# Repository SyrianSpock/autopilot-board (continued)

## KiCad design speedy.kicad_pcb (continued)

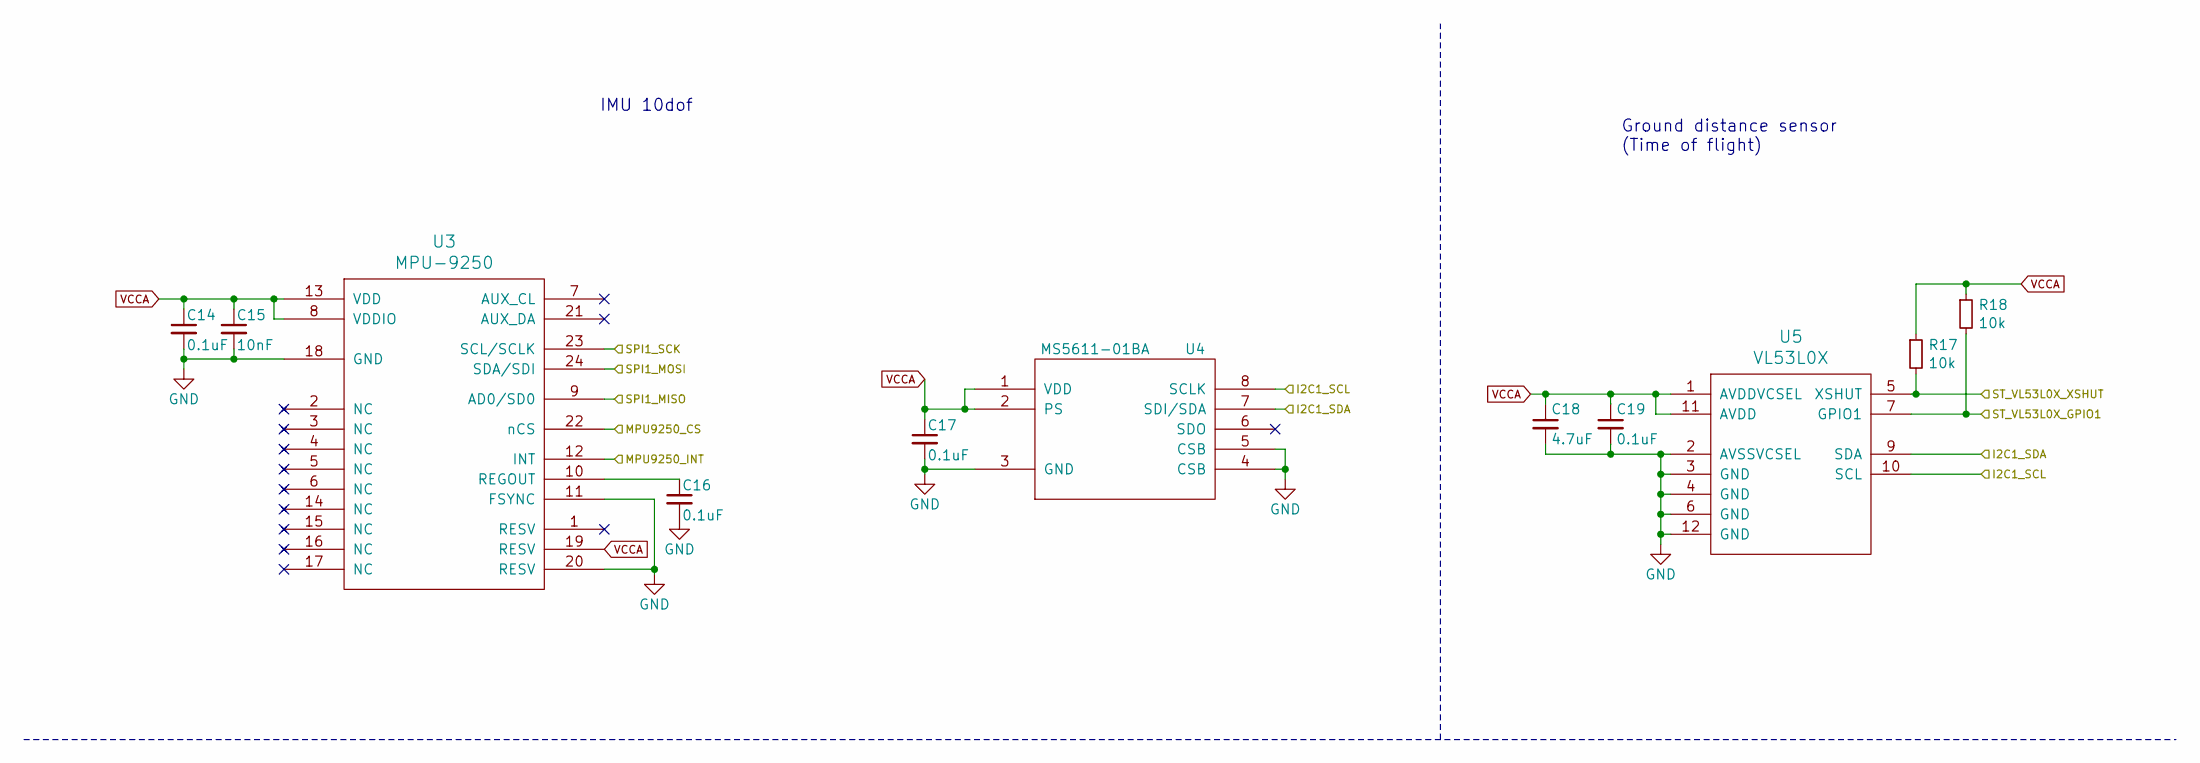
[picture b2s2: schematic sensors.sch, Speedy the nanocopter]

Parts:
C14, C16, C17, C19: 0.1uF; _0402
C15: 10nF; _0402
C18: 4.7uF; _0402
R17, R18: 10k; _0402
U3: MPU-9250; _MPU-9XX0
U4: MS5611-01BA; _MS5611-01BA
U5: VL53L0X; ST-VL53L0X

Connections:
/I2C1_SCL: U4.8 (SCLK), U5.10 (SCL); also elsewhere on the board
/I2C1_SDA: U4.7 (SDI/SDA), U5.9 (SDA); also elsewhere on the board
/MPU9250_CS: U3.22 (nCS); also elsewhere on the board
/MPU9250_INT: U3.12 (INT); also elsewhere on the board
/SPI1_MISO: U3.9 (AD0/SD0); also elsewhere on the board
/SPI1_MOSI: U3.24 (SDA/SDI); also elsewhere on the board
/SPI1_SCK: U3.23 (SCL/SCLK); also elsewhere on the board
/TOF_GPIO1: R18.2, U5.7 (GPIO1); also elsewhere on the board
/TOF_XSHUT: R17.2, U5.5 (XSHUT); also elsewhere on the board
GND: C14.2, C15.2, C16.2, C17.2, C18.2, C19.2, U3.11 (FSYNC), U3.18 (GND), U3.20 (RESV), U4.3 (GND), U4.4 (CSB), U4.5 (CSB), U5.2 (AVSSVCSEL), U5.3 (GND), U5.4 (GND), U5.6 (GND), U5.12 (GND); also elsewhere on the board
unnamed: C16.1, U3.10 (REGOUT)
VCCA: C14.1, C15.1, C17.1, C18.1, C19.1, R17.1, R18.1, U3.8 (VDDIO), U3.13 (VDD), U3.19 (RESV), U4.1 (VDD), U4.2 (PS), U5.1 (AVDDVCSEL), U5.11 (AVDD); also elsewhere on the board

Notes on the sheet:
Ground distance sensor (Time of flight)
IMU 10dof

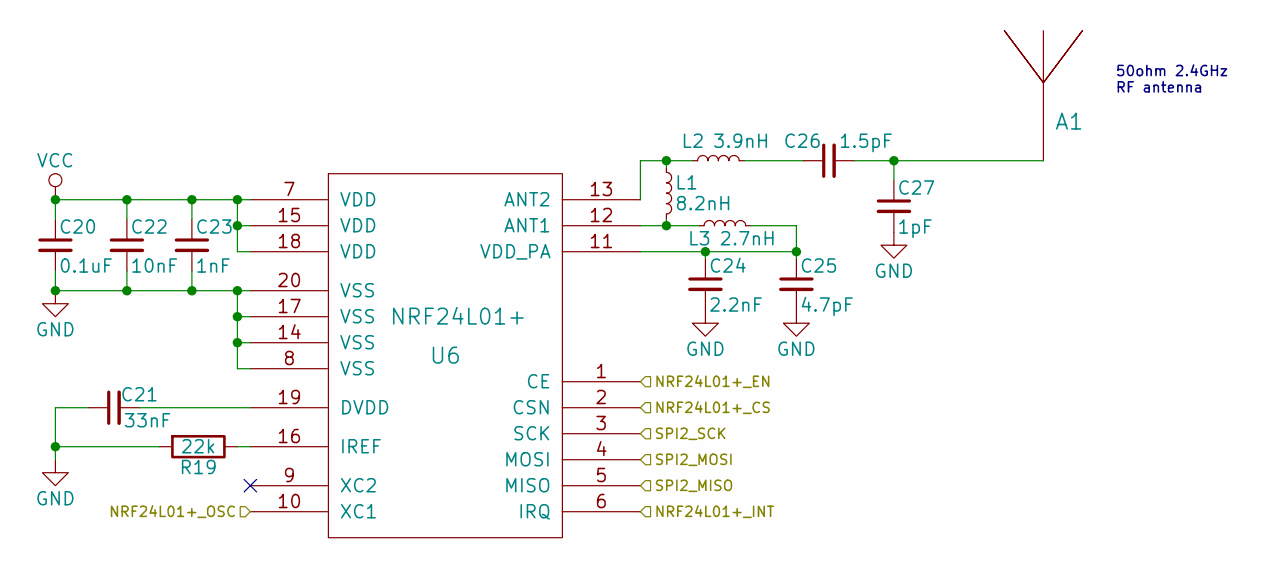
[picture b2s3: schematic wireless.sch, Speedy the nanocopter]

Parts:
A1: ANTENNA; _ANT-2.45-CHP
C20: 0.1uF; _0402
C21: 33nF; _0402
C22: 10nF; _0402
C23: 1nF; _0402
C24: 2.2nF; _0402
C25: 4.7pF; _0402
C26: 1.5pF; _0402
C27: 1pF; _0402
L1: 8.2nH; _0402
L2: 3.9nH; _0402
L3: 2.7nH; _0402
R19: 22k; _0402
U6: NRF24L01+; QFN-20-1EP_4x4mm_Pitch0.5mm

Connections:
/MCU_OSC_OUT: U6.10 (XC1); also elsewhere on the board
/NRF24L01+_CS: U6.2 (CSN); also elsewhere on the board
/NRF24L01+_EN: U6.1 (CE); also elsewhere on the board
/NRF24L01+_INT: U6.6 (IRQ); also elsewhere on the board
/SPI2_MISO: U6.5 (MISO); also elsewhere on the board
/SPI2_MOSI: U6.4 (MOSI); also elsewhere on the board
/SPI2_SCK: U6.3 (SCK); also elsewhere on the board
GND: C20.2, C21.1, C22.2, C23.2, C24.2, C25.2, C27.2, R19.2, U6.8 (VSS), U6.14 (VSS), U6.17 (VSS), U6.20 (VSS); also elsewhere on the board
unnamed: A1.1, C26.2, C27.1
unnamed: C21.2, U6.19 (DVDD)
unnamed: C24.1, C25.1, L3.2, U6.11 (VDD_PA)
unnamed: C26.1, L2.2
unnamed: L1.1, L2.1, U6.13 (ANT2)
unnamed: L1.2, L3.1, U6.12 (ANT1)
unnamed: R19.1, U6.16 (IREF)
VCC: C20.1, C22.1, C23.1, U6.7 (VDD), U6.15 (VDD), U6.18 (VDD); also elsewhere on the board

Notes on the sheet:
50ohm 2.4GHz RF antenna

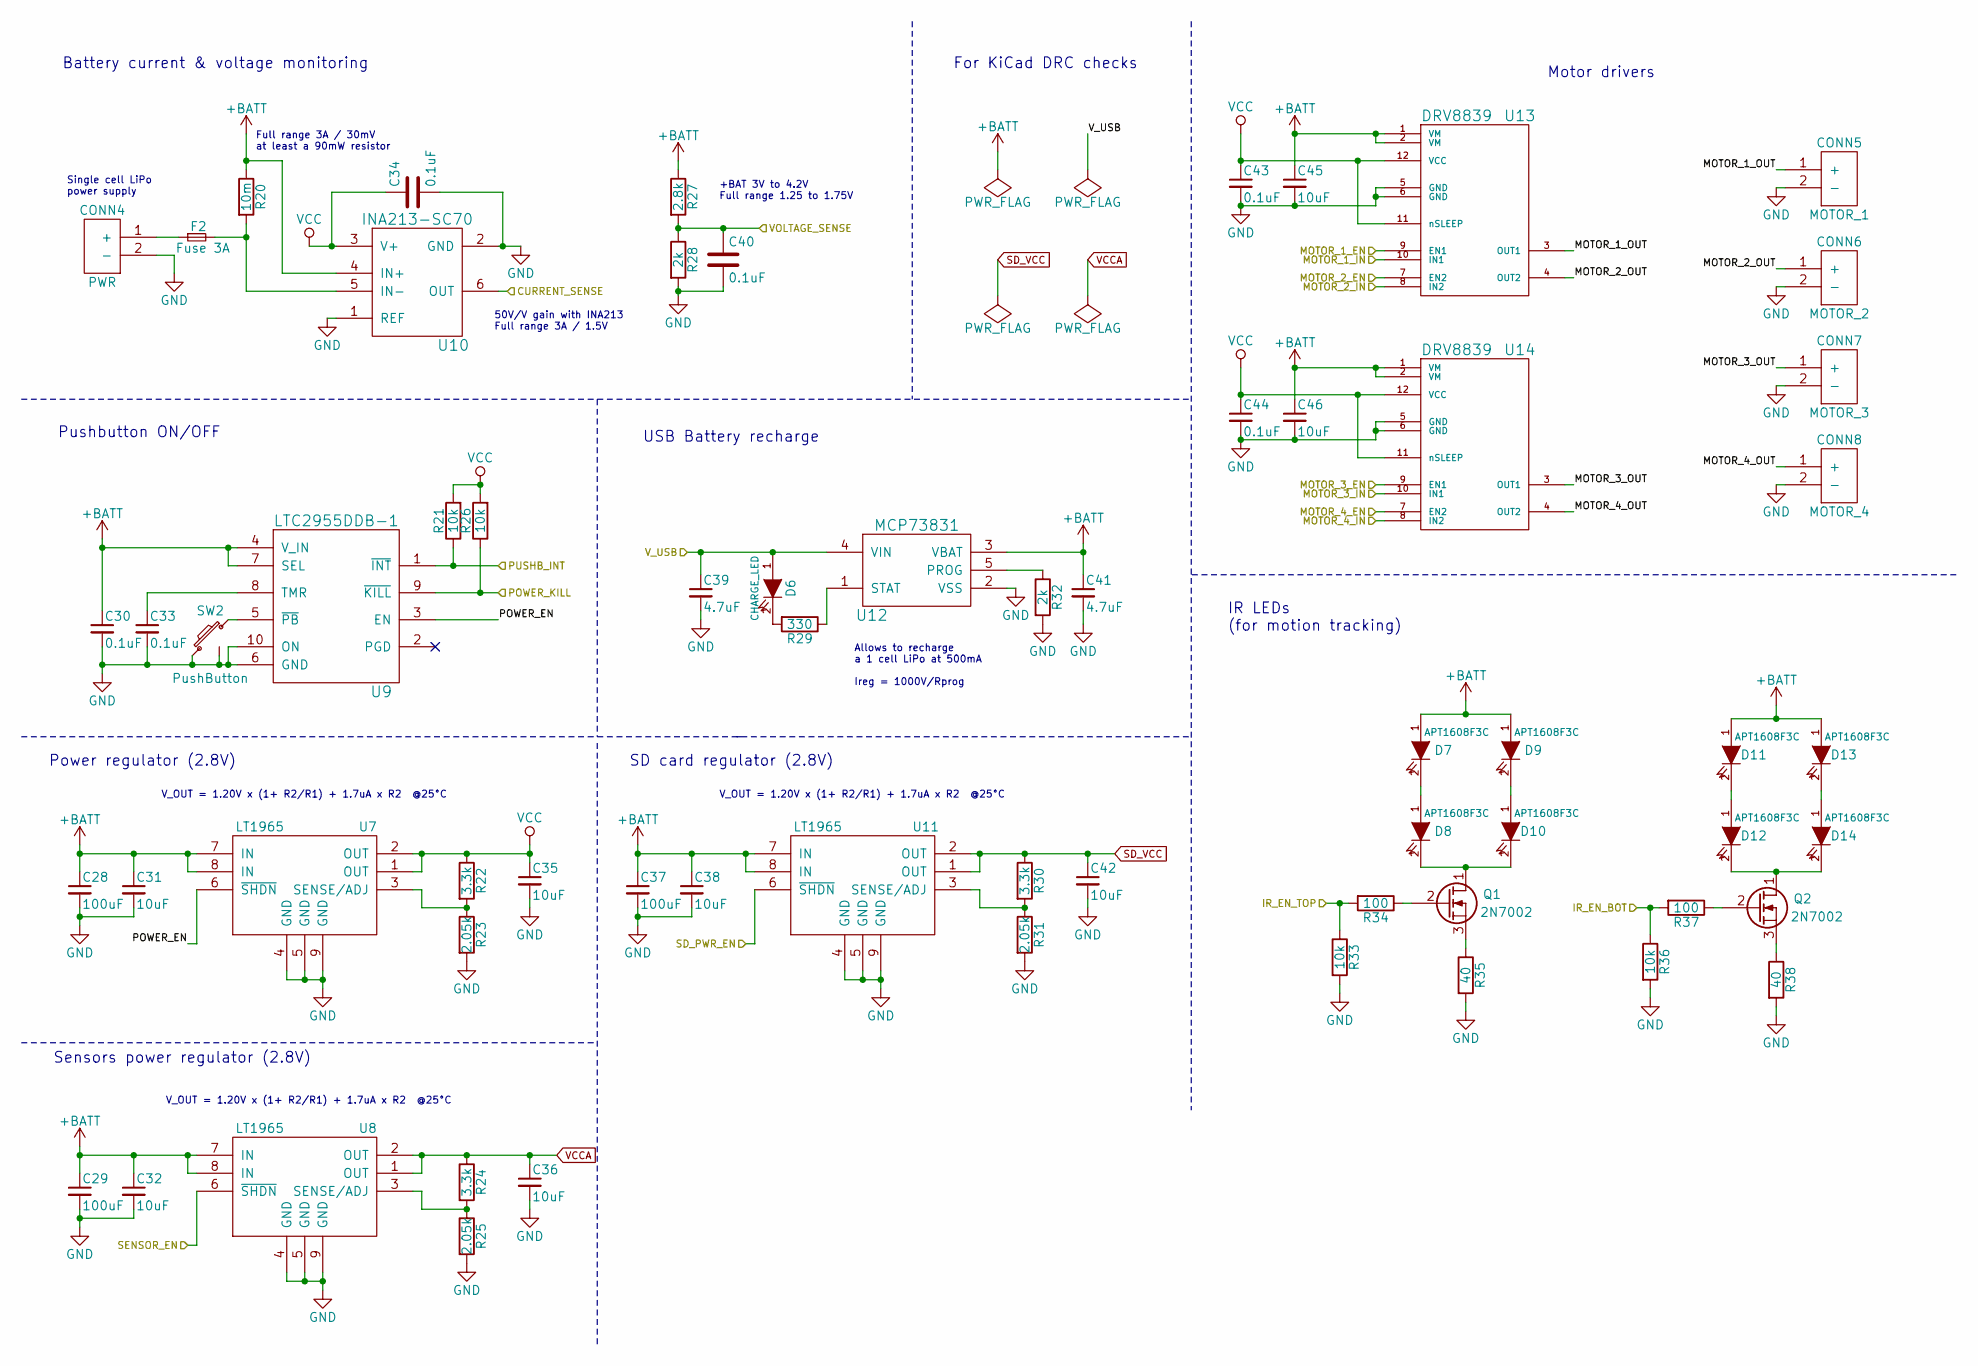
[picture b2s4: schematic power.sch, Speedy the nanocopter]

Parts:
C28, C29, C37: 100uF; _0603
C30, C33, C34, C40, C43, C44: 0.1uF; _0402
C31, C32, C35, C36, C38, C42, C45, C46: 10uF; _0603
C39, C41: 4.7uF; _0402
CONN4: PWR; _Pin2mm_2
CONN5: MOTOR_1; _Solder_Pad1.27_2
CONN6: MOTOR_2; _Solder_Pad1.27_2
CONN7: MOTOR_3; _Solder_Pad1.27_2
CONN8: MOTOR_4; _Solder_Pad1.27_2
D6: CHARGE_LED; _LED_0603
D7, D8, D9, D10, D11, D12, D13, D14: APT1608F3C; _LED_0603
F2: Fuse 3A; _0402
Q1, Q2: 2N7002; _SOT23-3
R20: 10m; _0402
R21, R26, R33, R36: 10k; _0402
R22, R24, R30: 3.3k; _0402
R23, R25, R31: 2.05k; _0402
R27: 2.8k; _0402
R28, R32: 2k; _0402
R29: 330; _0402
R34, R37: 100; _0402
R35, R38: 40; _0402
SW2: PushButton; SMD_Pushbutton_B3U-3100P
U7, U8, U11: LT1965; DFN-8-1EP_3x3mm_Pitch0.5mm
U9: LTC2955DDB-1; DFN-10-1EP_2x3mm_Pitch0.5mm
U10: INA213-SC70; SC70
U12: MCP73831; _TSOT23-5
U13, U14: DRV8839; TI-DRV8839_PWSON-N12

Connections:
+BATT: C28.1, C29.1, C30.1, C31.1, C32.1, C37.1, C38.1, C41.1, C45.1, C46.1, D7.1 (A), D9.1 (A), D11.1 (A), D13.1 (A), R20.1, R27.1, U7.7 (IN), U7.8 (IN), U8.7 (IN), U8.8 (IN), U9.4 (V_IN), U9.7 (SEL), U10.4 (IN+), U11.7 (IN), U11.8 (IN), U12.3 (VBAT), U13.1 (VM), U13.2 (VM), U14.1 (VM), U14.2 (VM)
/CURRENT_BAT_SENSE: U10.6 (OUT); also elsewhere on the board
/IR_EN_BOTTOM: R36.1, R37.2; also elsewhere on the board
/IR_EN_TOP: R33.1, R34.2; also elsewhere on the board
/MOTOR_1_EN: U13.9 (EN1); also elsewhere on the board
/MOTOR_1_IN: U13.10 (IN1); also elsewhere on the board
/MOTOR_2_EN: U13.7 (EN2); also elsewhere on the board
/MOTOR_2_IN: U13.8 (IN2); also elsewhere on the board
/MOTOR_3_EN: U14.9 (EN1); also elsewhere on the board
/MOTOR_3_IN: U14.10 (IN1); also elsewhere on the board
/MOTOR_4_EN: U14.7 (EN2); also elsewhere on the board
/MOTOR_4_IN: U14.8 (IN2); also elsewhere on the board
/POWER_KILL: R26.1, U9.9 (~KILL); also elsewhere on the board
/PUSHBUTTON_INT: R21.1, U9.1 (~INT); also elsewhere on the board
/Power/MOTOR_1_OUT: CONN5.1 (+), U13.3 (OUT1)
/Power/MOTOR_2_OUT: CONN6.1 (+), U13.4 (OUT2)
/Power/MOTOR_3_OUT: CONN7.1 (+), U14.3 (OUT1)
/Power/MOTOR_4_OUT: CONN8.1 (+), U14.4 (OUT2)
/Power/POWER_EN: U7.6 (~SHDN), U9.3 (EN)
/SD_PWR_EN: U11.6 (~SHDN); also elsewhere on the board
/SENSOR_PWR_ON: U8.6 (~SHDN); also elsewhere on the board
/VOLTAGE_BAT_SENSE: C40.1, R27.2, R28.1; also elsewhere on the board
/V_USB: C39.1, D6.1 (A), U12.4 (VIN); also elsewhere on the board
GND: C28.2, C29.2, C30.2, C31.2, C32.2, C33.2, C34.2, C35.2, C36.2, C37.2, C38.2, C39.2, C40.2, C41.2, C42.2, C43.2, C44.2, C45.2, C46.2, CONN4.2 (-), CONN5.2 (-), CONN6.2 (-), CONN7.2 (-), CONN8.2 (-), R23.2, R25.2, R28.2, R31.2, R32.2, R33.2, R35.2, R36.2, R38.2, SW2.2, SW2.3 (GND), U7.4 (GND), U7.5 (GND), U7.9 (GND), U8.4 (GND), U8.5 (GND), U8.9 (GND), U9.6 (GND), U9.10 (ON), U10.1 (REF), U10.2 (GND), U11.4 (GND), U11.5 (GND), U11.9 (GND), U12.2 (VSS), U13.5 (GND), U13.6 (GND), U14.5 (GND), U14.6 (GND); also elsewhere on the board
unnamed: C33.1, U9.8 (TMR)
unnamed: CONN4.1 (+), F2.1
unnamed: D6.2 (K), R29.2
unnamed: D7.2 (K), D8.1 (A)
unnamed: D9.2 (K), D10.1 (A)
unnamed: D8.2 (K), D10.2 (K), Q1.1 (D)
unnamed: D11.2 (K), D12.1 (A)
unnamed: D12.2 (K), D14.2 (K), Q2.1 (D)
unnamed: D13.2 (K), D14.1 (A)
unnamed: F2.2, R20.2, U10.5 (IN-)
unnamed: Q1.2 (G), R34.1
unnamed: Q1.3 (S), R35.1
unnamed: Q2.2 (G), R37.1
unnamed: Q2.3 (S), R38.1
unnamed: R22.2, R23.1, U7.3 (SENSE/ADJ)
unnamed: R24.2, R25.1, U8.3 (SENSE/ADJ)
unnamed: R29.1, U12.1 (STAT)
unnamed: R30.2, R31.1, U11.3 (SENSE/ADJ)
unnamed: R32.1, U12.5 (PROG)
unnamed: SW2.1, U9.5 (~PB)
SD_VCC: C42.1, R30.1, U11.1 (OUT), U11.2 (OUT); also elsewhere on the board
VCC: C34.1, C35.1, C43.1, C44.1, R21.2, R22.1, R26.2, U7.1 (OUT), U7.2 (OUT), U10.3 (V+), U13.11 (nSLEEP), U13.12 (VCC), U14.11 (nSLEEP), U14.12 (VCC); also elsewhere on the board
VCCA: C36.1, R24.1, U8.1 (OUT), U8.2 (OUT); also elsewhere on the board

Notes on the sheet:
Allows to recharge a 1 cell LiPo at 500mA Ireg = 1000V/Rprog
V_OUT = 1.20V x (1+ R2/R1) + 1.7uA x R2 @25°C
Single cell LiPo power supply
Full range 3A / 30mV at least a 90mW resistor
50V/V gain with INA213 Full range 3A / 1.5V
+BAT 3V to 4.2V Full range 1.25 to 1.75V
Battery current & voltage monitoring
Power regulator (2.8V)
Pushbutton ON/OFF
USB Battery recharge
Motor drivers
IR LEDs (for motion tracking)
For KiCad DRC checks
Sensors power regulator (2.8V)
SD card regulator (2.8V)

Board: 2 copper layers, 131 parts (61 on the bottom side), 102 nets, no tracks yet.

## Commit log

2015-03-23 Block diagram
2015-03-23 Preliminary choice of components
2015-03-24 Add Kicad library as submodule
2015-03-26 Remove camera from autopilot board
2015-04-16 Updating features description
2015-04-17 Add PCB shape
2015-04-21 Add STM32F4 MCU to schematics
2015-04-21 Datasheets update
2015-04-21 Add oscillator
2015-04-21 Add MPU 9250
2015-04-21 Adjust MPU9250 wiring to MCU
2015-04-21 Add ground sensor (VL6180X)
2015-04-21 Update datasheets
2015-04-22 Change radio component datasheet
2015-04-22 Add level shifters for i2c of TOF sensor
2015-04-22 Add power regulator 2.8V for VL6180 TOF sensor
2015-04-22 LiPo recharge circuit
2015-04-22 Update schematic labels to handle hierarchical signal dependencies
2015-04-22 Add principal power supply
2015-04-22 Barometer in schematic
2015-04-22 uSD card added to schematics
2015-04-25 CAN transceiver added in schematics
2015-04-25 Motors & drivers TI drv8839 (independent pwm) added to schematics
2015-04-25 Second CAN connector for daisy chain
2015-04-25 Connect motors to timer 1
2015-04-28 nRF24L01+ integrated + correct capacitors
2015-05-01 Move nrf24 to separate sheet and Add USB termination
2015-05-01 Add pushbutton power management
2015-05-01 Add IR Leds on top and bottom with enable on MCU
2015-05-02 PCB outline (updated)
2015-05-02 Documentation (datasheets) reordering
2015-05-02 Battery monitoring (voltage and current sense)
2015-05-02 Add debug interface (JTAG, UART, LEDs)
2015-05-25 Annotation
2015-06-27 Change MCU to LQFP64 (instead of BGA)
2015-06-27 Minor corrections
    Wire GPIO of VL6180X to MCU
    Remove UART4
    Change Shottky diode
    Add fuse on CAN bus power
2015-06-27 Netlist
2015-06-27 More datasheets
2015-06-30 Remove CAN interface
    (not useful enough, takes too much place)
2015-08-10 Use JTAG instead of SWD
2015-09-03 Update specifications
2015-09-03 Remove SD card
2016-01-19 Revert "Remove SD card"
    This reverts commit 4a1918bee256f93cb8d66746410e6c192988175c.
2016-01-19 Regenerate netlist & Start placing footprints
2016-01-21 Finish placing components on PCB
2016-01-21 Draw edge cuts
2016-01-21 Update pdf schematics
2016-01-21 Checkin kicad pointer library table
2016-01-28 Change pushbutton for a radially mounted button
2016-01-29 Change micro USB connector & add 3d models to some footprints
2016-02-01 Replot schematic pdf for review
2016-02-01 Add missing datasheets
2016-02-01 Update project documentation / diagram
2016-02-02 Move SDIO pullups from clock to CMD
    see NXP AN10911 http://www.nxp.com/documents/application_note/AN10911.pdf
2016-02-02 Correct boot pattern to enable DFU
    Add a push button to VCC on Boot0 to accomplish pattern 1 from AN2606
    Previous configuration wouldn't have worked to trigger DFU as noted by @nuft
2016-02-19 Fix problems noted by @nuft during review
    - Force pulldown on unused bootloadr pins (USART 1 & 3)
    - Use one oscillator for both MCU and NRF
2016-02-20 (Re)Place components on PCB
    Netlist was broken after review corrections
    Rebuilt and placed components from scratch
2016-06-04 Update debug connector to use new CVRA convention
    SWD + UART connector using Molex picoblade 7pin connector
2016-06-04 Update TOF sensor to use new ST VL53L0X with 2m range
2016-06-04 Update footprints/netlist
2016-06-04 Update pdf schematic
2016-06-05 Update form to square PCB, place components and update 3D models
2016-06-23 Reorganise files
2016-06-25 Use wifi for telemetry
    Cleanup schematic
    Use ESP12E (wifi) for telemetry instead of NRF24
    Reannotate & replot pdf
2016-06-25 Place components again after schematic update
    Increase size of board to 40mmx40mm
2016-06-26 Update with small corrections
    Decrease LED resistor values
    Fix NUF2042 name
    Fix MPU9250 wiring (contradictory datasheet)
2016-07-21 Finish routing
2016-07-21 Plot gerber files
